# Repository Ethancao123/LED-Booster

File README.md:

# LED-Booster

An LED board for FRC designed to be used with the Limelight.

The board is single layer to allow for the use aluminum base PCBs.

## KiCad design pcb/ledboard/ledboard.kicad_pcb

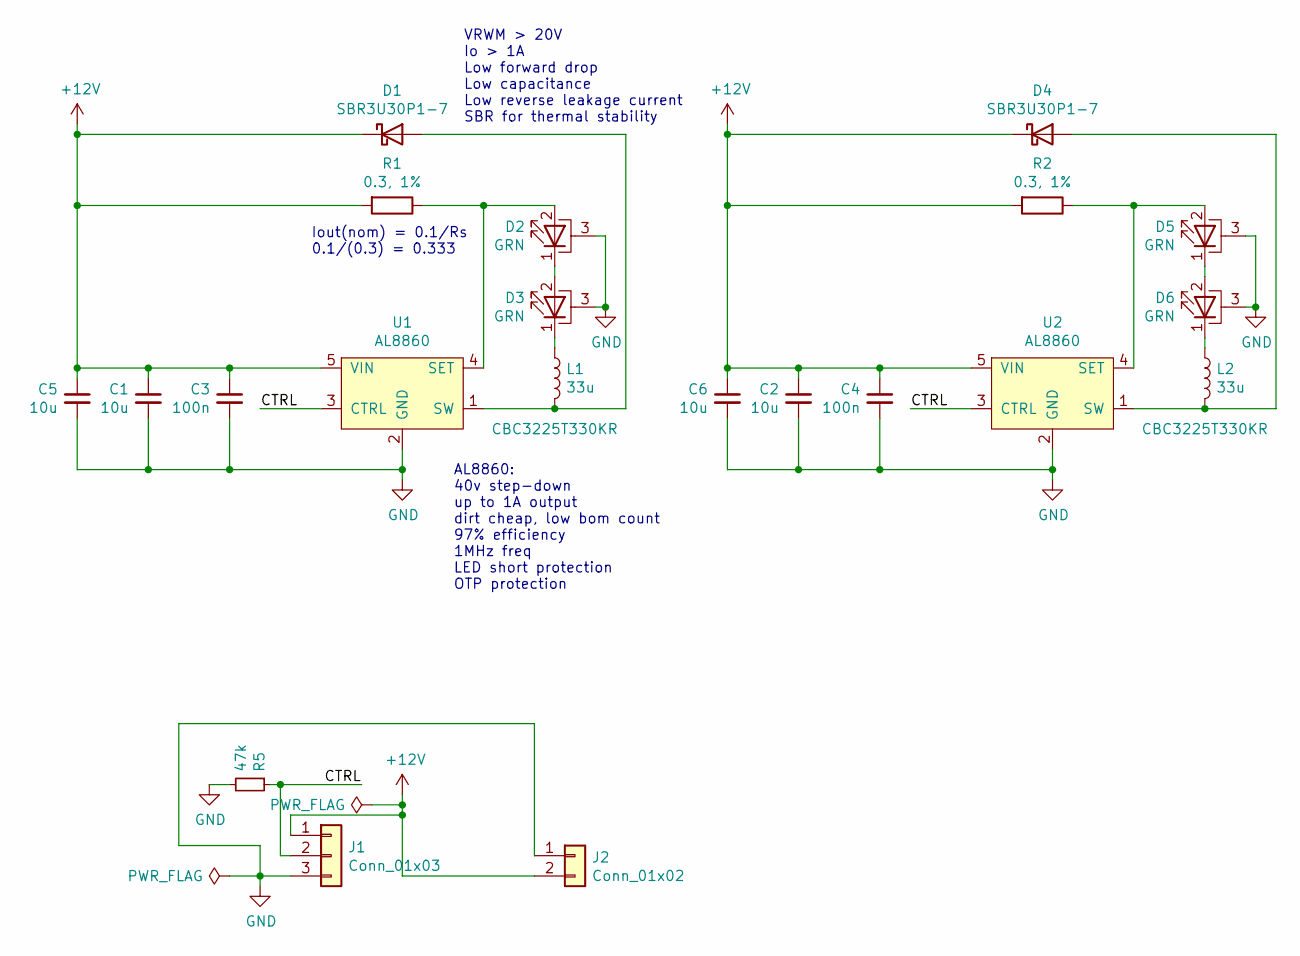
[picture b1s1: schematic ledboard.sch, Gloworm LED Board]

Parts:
C1, C2, C5, C6: 10u; C_0603_1608Metric; LCSC C96446
C3, C4: 100n; C_0603_1608Metric; LCSC C106256
D1, D4: SBR3U30P1-7; D_PowerDI-123; LCSC C110517
D2, D3, D5, D6: GRN; LED_1W_3W_R8
J1: Conn_01x03; WJ250B-3pin
J2: Conn_01x02; AMASS_XT30U-M_1x02_P5.0mm_Vertical
L1, L2: 33u; L_1210_3225Metric; LCSC C223226
R1, R2: 0.3, 1%; R_0805_2012Metric; LCSC C247157
R5: 47k; R_0603_1608Metric; LCSC C25563
U1, U2: AL8860; TSOT-23-5_RoundRect; LCSC C125330

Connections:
+12V: C1.1, C2.1, C3.1, C4.1, C5.1, C6.1, D1.1 (K), D4.1 (K), J1.1, J2.2, R1.2, R2.2, U1.5 (VIN), U2.5 (VIN)
/CTRL: J1.2, R5.1, U1.3 (CTRL), U2.3 (CTRL)
GND: C1.2, C2.2, C3.2, C4.2, C5.2, C6.2, D2.3 (PAD), D3.3 (PAD), D5.3 (PAD), D6.3 (PAD), J1.3, J2.1, R5.2, U1.2 (GND), U2.2 (GND)
unnamed: D1.2 (A), L1.2, U1.1 (SW)
unnamed: D2.1 (K), D3.2 (A)
unnamed: D2.2 (A), R1.1, U1.4 (SET)
unnamed: D3.1 (K), L1.1
unnamed: D4.2 (A), L2.2, U2.1 (SW)
unnamed: D5.1 (K), D6.2 (A)
unnamed: D5.2 (A), R2.1, U2.4 (SET)
unnamed: D6.1 (K), L2.1

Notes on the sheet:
Iout(nom) = 0.1/Rs 0.1/(0.3) = 0.333
VRWM > 20V Io > 1A Low forward drop Low capacitance Low reverse leakage current SBR for thermal stability
AL8860: 40v step-down up to 1A output dirt cheap, low bom count 97% efficiency 1MHz freq LED short protection OTP protection

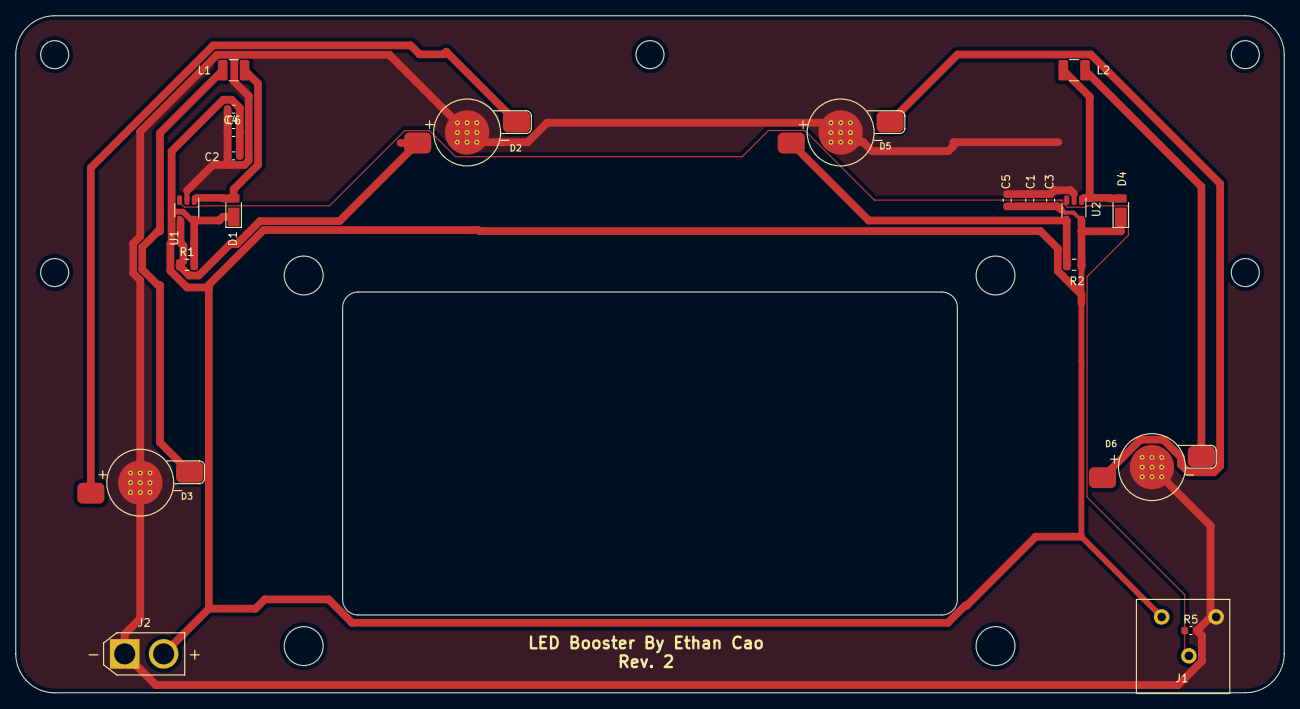
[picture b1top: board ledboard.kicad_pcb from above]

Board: 2 copper layers, 163.0 x 87.0 mm, 21 parts (0 on the bottom side), 11 nets.

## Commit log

2021-12-10 Cleaned up files
2021-12-11 Created LED Board
2021-12-11 Added images
2021-12-11 Finished pcb
2021-12-30 [ImgBot] Optimize images
    *Total -- 1,018.41kb -> 984.80kb (3.3%)
    /img/PCB.png -- 85.49kb -> 72.63kb (15.05%)
    /img/3D.png -- 932.92kb -> 912.17kb (2.22%)
2021-12-30 Added image
2022-03-29 started v2
2022-03-29 [ImgBot] Optimize images
    *Total -- 410.11kb -> 356.19kb (13.15%)
    /pcb/ledboard/ledboard-brd.svg -- 46.48kb -> 37.47kb (19.39%)
    /img/PCB.png -- 85.49kb -> 72.63kb (15.05%)
    /img/LEDBooster.jpg -- 278.13kb -> 246.10kb (11.52%)
2022-03-30 ledboard kinda done???

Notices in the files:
pcb/ledboard/ledboard.kicad_pcb:
Copyright Franklin Harding 2020
Licensed under CERN-OHL-P v2
